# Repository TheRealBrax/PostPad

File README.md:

# PostPad
A compact, programmable control pad for video editors.

##AI Disclosure:
During this project, I used AI to help with debugging and to assist in writing firmware.

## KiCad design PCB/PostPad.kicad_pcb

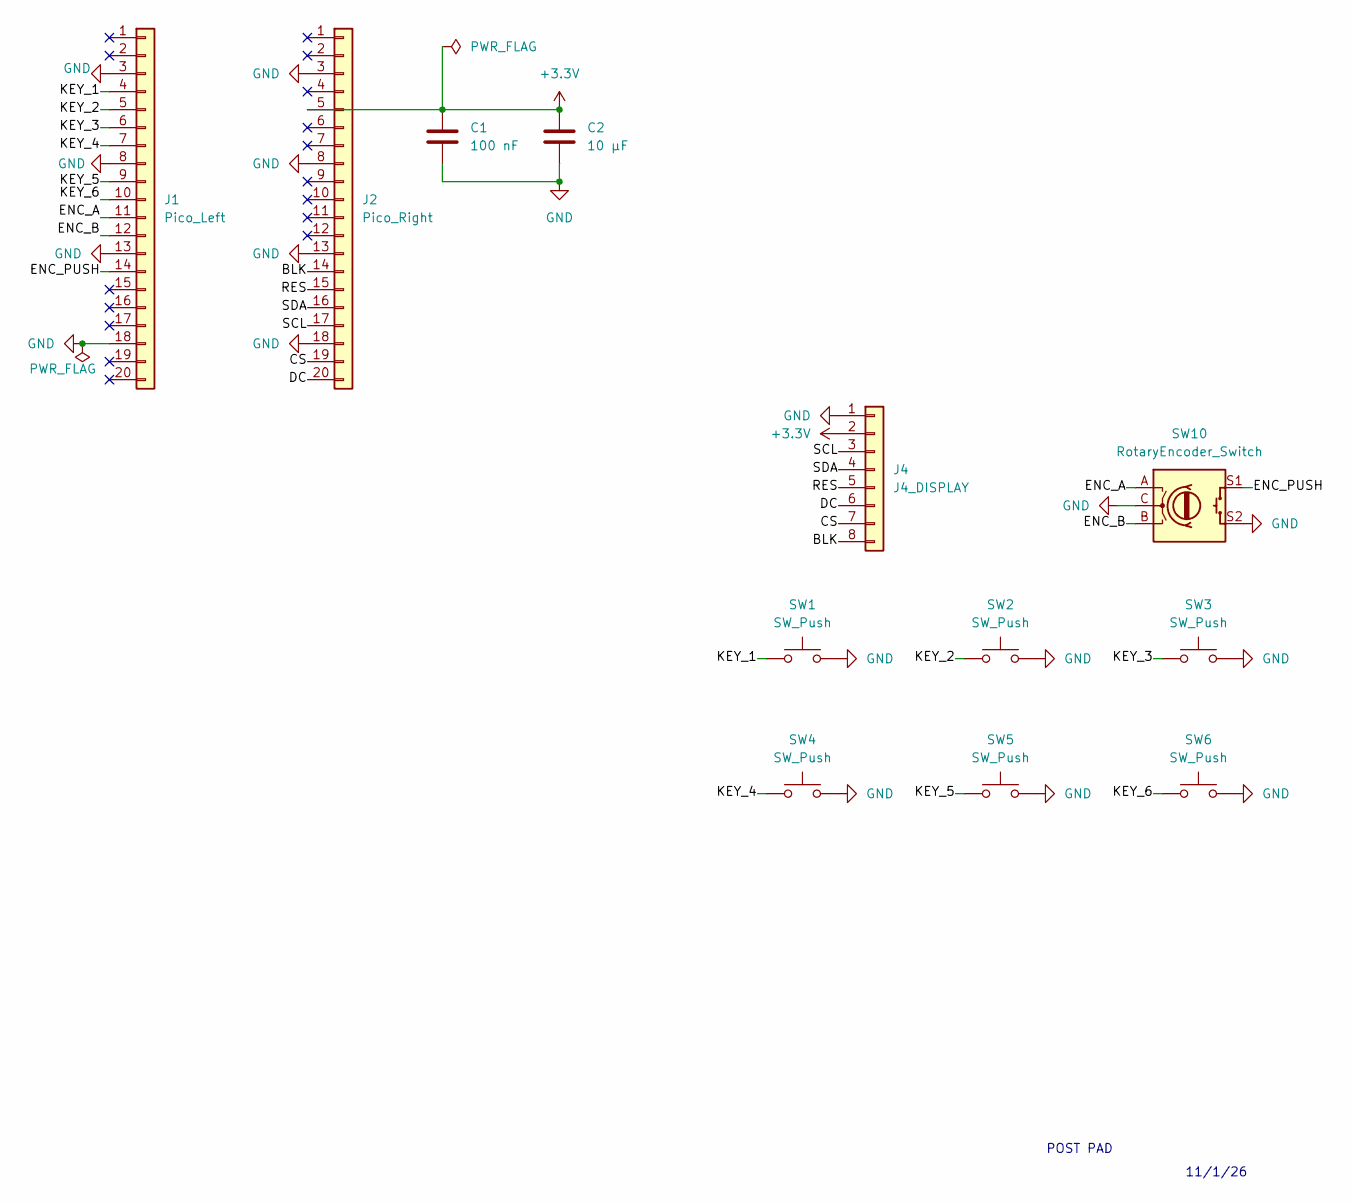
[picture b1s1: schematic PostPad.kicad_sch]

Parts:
C1: 100 nF; C_0603_1608Metric
C2: 10 µF; C_0805_2012Metric
J1: Pico_Left; PinSocket_1x20_P2.54mm_Vertical
J2: Pico_Right; PinSocket_1x20_P2.54mm_Vertical
J4: J4_DISPLAY; PinSocket_1x08_P2.54mm_Vertical
SW1, SW2, SW3, SW4, SW5, SW6: SW_Push; SW_Cherry_MX_1.00u_PCB
SW10: RotaryEncoder_Switch; RotaryEncoder_Alps_EC11E-Switch_Vertical_H20mm

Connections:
+3.3V: C1.1, C2.1, J2.5, J4.2
/BLK: J2.14, J4.8
/CS: J2.19, J4.7
/DC: J2.20, J4.6
/ENC_A: J1.11, SW10.A
/ENC_B: J1.12, SW10.B
/ENC_PUSH: J1.14, SW10.S1
/KEY_1: J1.4, SW1.1
/KEY_2: J1.5, SW2.1
/KEY_3: J1.6, SW3.1
/KEY_4: J1.7, SW4.1
/KEY_5: J1.9, SW5.1
/KEY_6: J1.10, SW6.1
/RES: J2.15, J4.5
/SCL: J2.17, J4.3
/SDA: J2.16, J4.4
GND: C1.2, C2.2, J1.3, J1.8, J1.13, J1.18, J2.3, J2.8, J2.13, J2.18, J4.1, SW1.2, SW2.2, SW3.2, SW4.2, SW5.2, SW6.2, SW10.C, SW10.S2

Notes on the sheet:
11/1/26
POST PAD

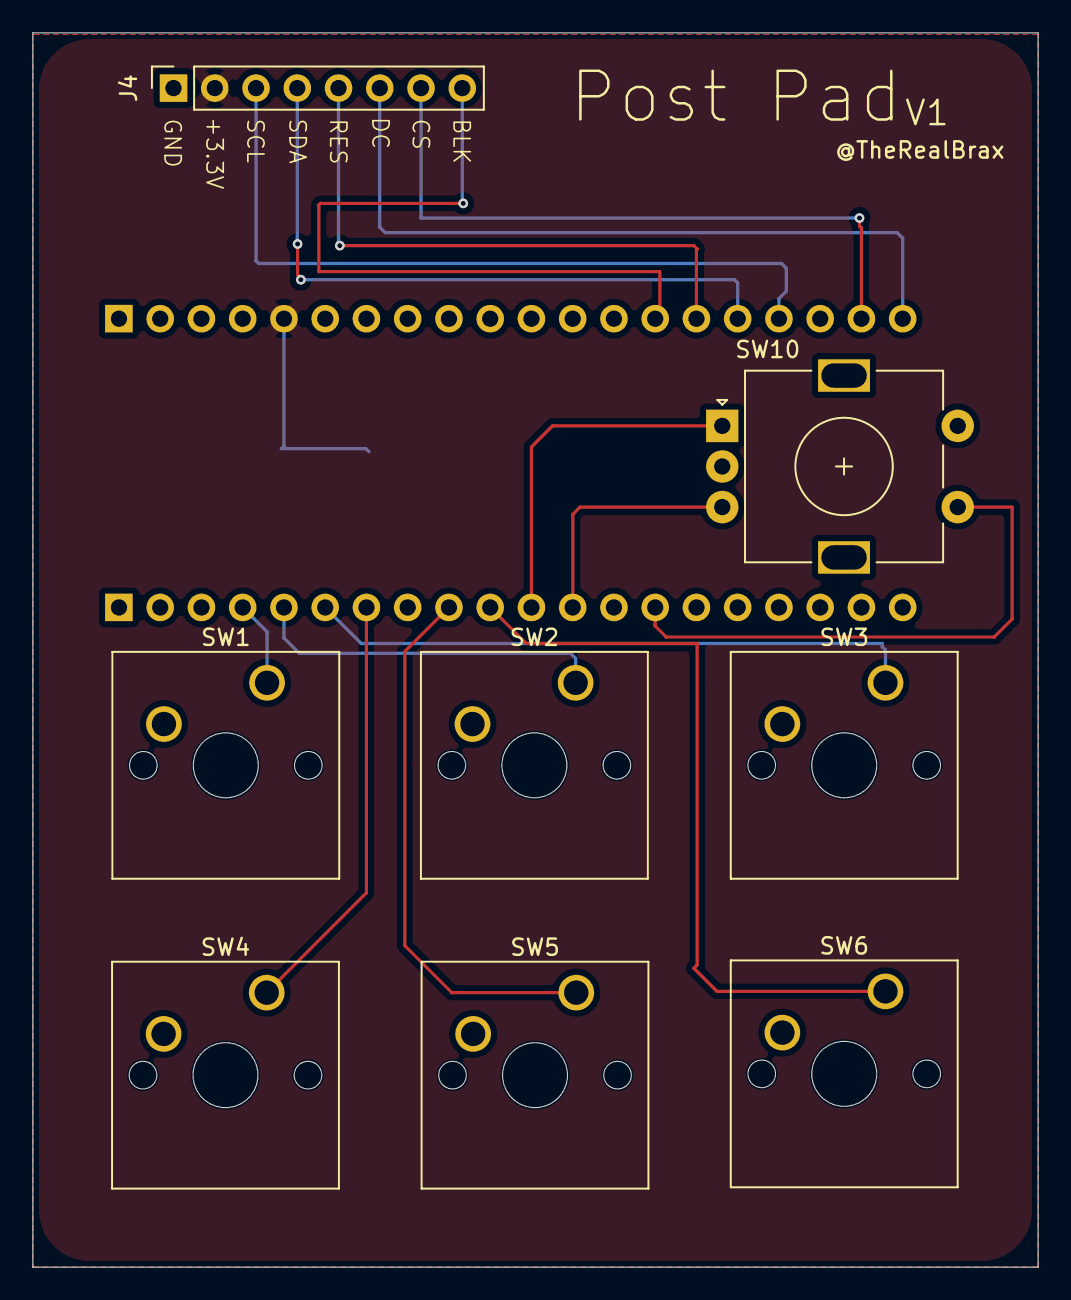
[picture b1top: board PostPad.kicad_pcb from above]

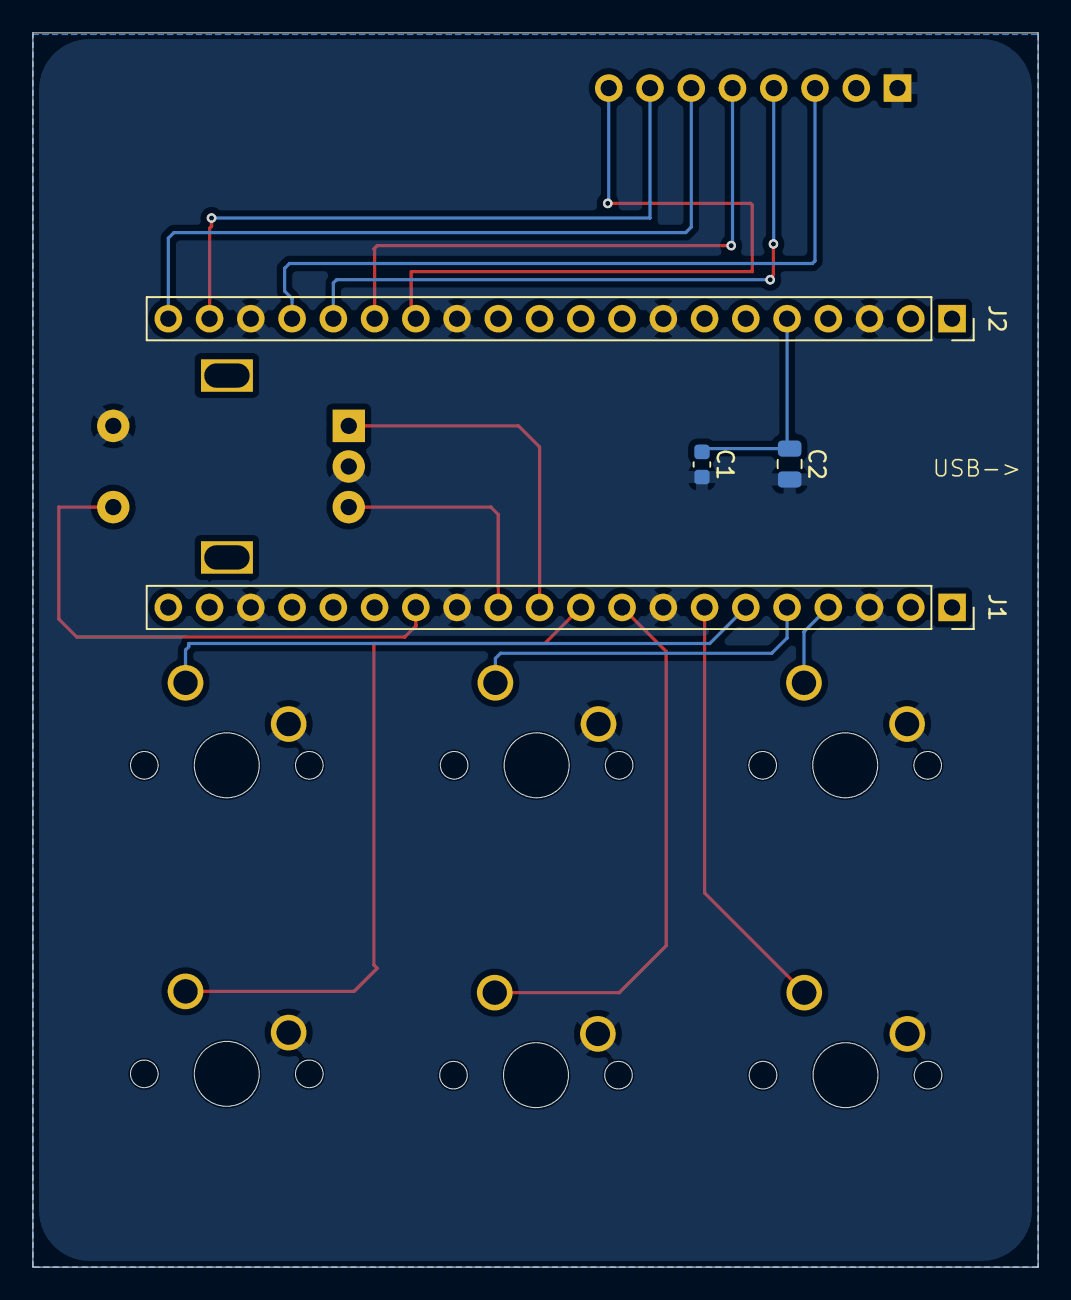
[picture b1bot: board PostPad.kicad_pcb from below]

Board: 2 copper layers, 61.9 x 76.0 mm, 12 parts (4 on the bottom side), 17 nets.
